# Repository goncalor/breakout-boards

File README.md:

Right now please do not trust what is on this repository. Thank you.

# breakout-boards
A collection of breakout boards

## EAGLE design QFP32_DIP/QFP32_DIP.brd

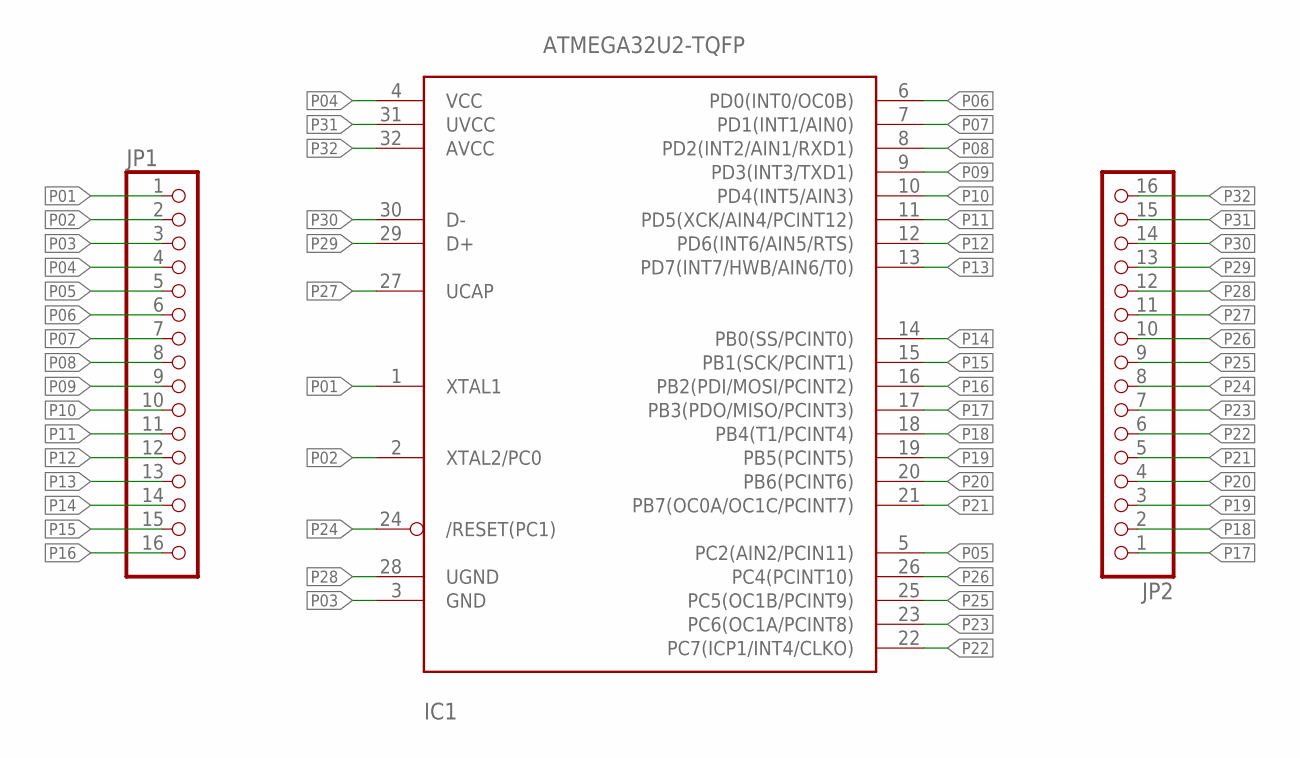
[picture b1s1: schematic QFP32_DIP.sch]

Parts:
IC1: ATMEGA32U2-TQFP; TQFP32-08
JP1, JP2: PINHD-1X16; 1X16

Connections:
P01: IC1.1 (XTAL1), JP1.1
P02: IC1.2 (XTAL2/PC0), JP1.2
P03: IC1.3 (GND), JP1.3
P04: IC1.4 (VCC), JP1.4
P05: IC1.5 (PC2(AIN2/PCIN11)), JP1.5
P06: IC1.6 (PD0(INT0/OC0B)), JP1.6
P07: IC1.7 (PD1(INT1/AIN0)), JP1.7
P08: IC1.8 (PD2(INT2/AIN1/RXD1)), JP1.8
P09: IC1.9 (PD3(INT3/TXD1)), JP1.9
P10: IC1.10 (PD4(INT5/AIN3)), JP1.10
P11: IC1.11 (PD5(XCK/AIN4/PCINT12)), JP1.11
P12: IC1.12 (PD6(INT6/AIN5/RTS)), JP1.12
P13: IC1.13 (PD7(INT7/HWB/AIN6/T0)), JP1.13
P14: IC1.14 (PB0(SS/PCINT0)), JP1.14
P15: IC1.15 (PB1(SCK/PCINT1)), JP1.15
P16: IC1.16 (PB2(PDI/MOSI/PCINT2)), JP1.16
P17: IC1.17 (PB3(PDO/MISO/PCINT3)), JP2.1
P18: IC1.18 (PB4(T1/PCINT4)), JP2.2
P19: IC1.19 (PB5(PCINT5)), JP2.3
P20: IC1.20 (PB6(PCINT6)), JP2.4
P21: IC1.21 (PB7(OC0A/OC1C/PCINT7)), JP2.5
P22: IC1.22 (PC7(ICP1/INT4/CLKO)), JP2.6
P23: IC1.23 (PC6(OC1A/PCINT8)), JP2.7
P24: IC1.24 (/RESET(PC1)), JP2.8
P25: IC1.25 (PC5(OC1B/PCINT9)), JP2.9
P26: IC1.26 (PC4(PCINT10)), JP2.10
P27: IC1.27 (UCAP), JP2.11
P28: IC1.28 (UGND), JP2.12
P29: IC1.29 (D+), JP2.13
P30: IC1.30 (D-), JP2.14
P31: IC1.31 (UVCC), JP2.15
P32: IC1.32 (AVCC), JP2.16

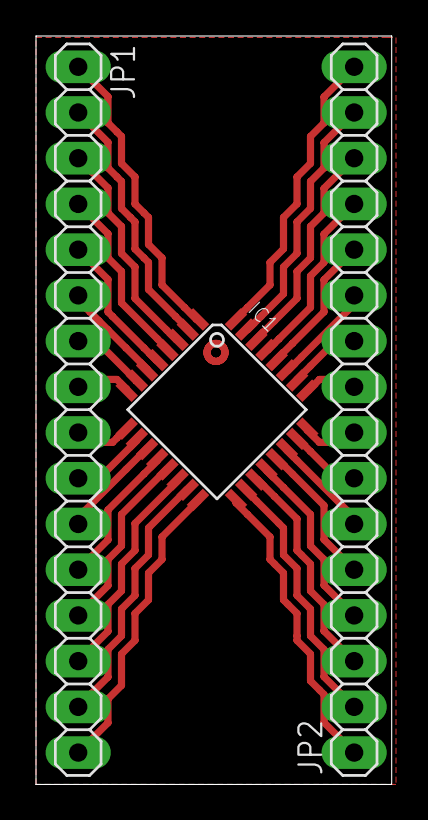
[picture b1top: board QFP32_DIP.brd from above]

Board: 2 copper layers, 19.8 x 41.6 mm, 3 parts (0 on the bottom side), 32 nets.

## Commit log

2015-07-06 Added QFP32 to DIP. Header spacing could b impoved
